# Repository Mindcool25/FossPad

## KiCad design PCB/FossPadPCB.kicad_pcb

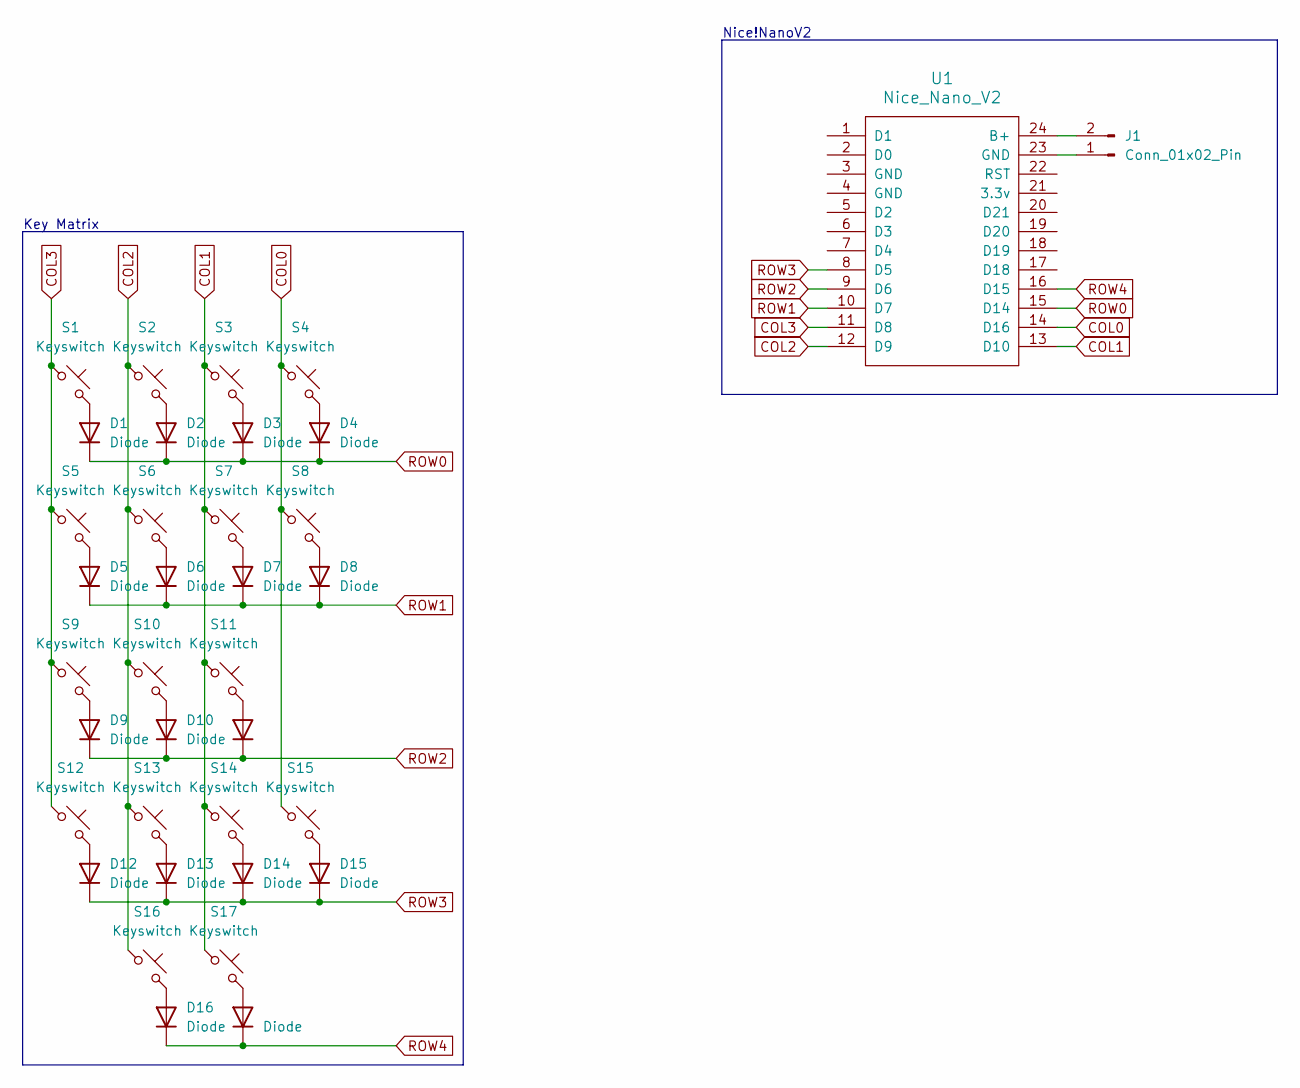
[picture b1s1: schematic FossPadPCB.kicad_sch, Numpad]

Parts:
D1, D2, D3, D4, D5, D6, D7, D8, D9, D10, D11, D12, D13, D14, D15, D16, D17: Diode; Diode_DO-35
J1: Conn_01x02_Pin; JWT_A3963_1x02_P3.96mm_Vertical
S1, S2, S3, S4, S5, S6, S7, S9, S10, S11, S12, S13, S14, S17: Keyswitch; MX_PCB_1.00u
S8, S15: Keyswitch; MX_PCB_2.00u_90deg
S16: Keyswitch; MX_PCB_2.00u
U1: Nice_Nano_V2

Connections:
COL0: S4.1, S8.1, S15.1, U1.14 (D16)
COL1: S3.1, S7.1, S11.1, S14.1, S17.1, U1.13 (D10)
COL2: S2.1, S6.1, S10.1, S13.1, S16.1, U1.12 (D9)
COL3: S1.1, S5.1, S9.1, S12.1, U1.11 (D8)
unnamed: D1.2 (A), S1.2
unnamed: D2.2 (A), S2.2
unnamed: D3.2 (A), S3.2
unnamed: D4.2 (A), S4.2
unnamed: D5.2 (A), S5.2
unnamed: D6.2 (A), S6.2
unnamed: D7.2 (A), S7.2
unnamed: D8.2 (A), S8.2
unnamed: D9.2 (A), S9.2
unnamed: D10.2 (A), S10.2
unnamed: D11.2 (A), S11.2
unnamed: D12.2 (A), S12.2
unnamed: D13.2 (A), S13.2
unnamed: D14.2 (A), S14.2
unnamed: D15.2 (A), S15.2
unnamed: D16.2 (A), S16.2
unnamed: D17.2 (A), S17.2
unnamed: J1.1, U1.23 (GND)
unnamed: J1.2, U1.24 (B+)
ROW0: D1.1 (K), D2.1 (K), D3.1 (K), D4.1 (K), U1.15 (D14)
ROW1: D5.1 (K), D6.1 (K), D7.1 (K), D8.1 (K), U1.10 (D7)
ROW2: D9.1 (K), D10.1 (K), D11.1 (K), U1.9 (D6)
ROW3: D12.1 (K), D13.1 (K), D14.1 (K), D15.1 (K), U1.8 (D5)
ROW4: D16.1 (K), D17.1 (K), U1.16 (D15)

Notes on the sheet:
Key Matrix
Nice!NanoV2

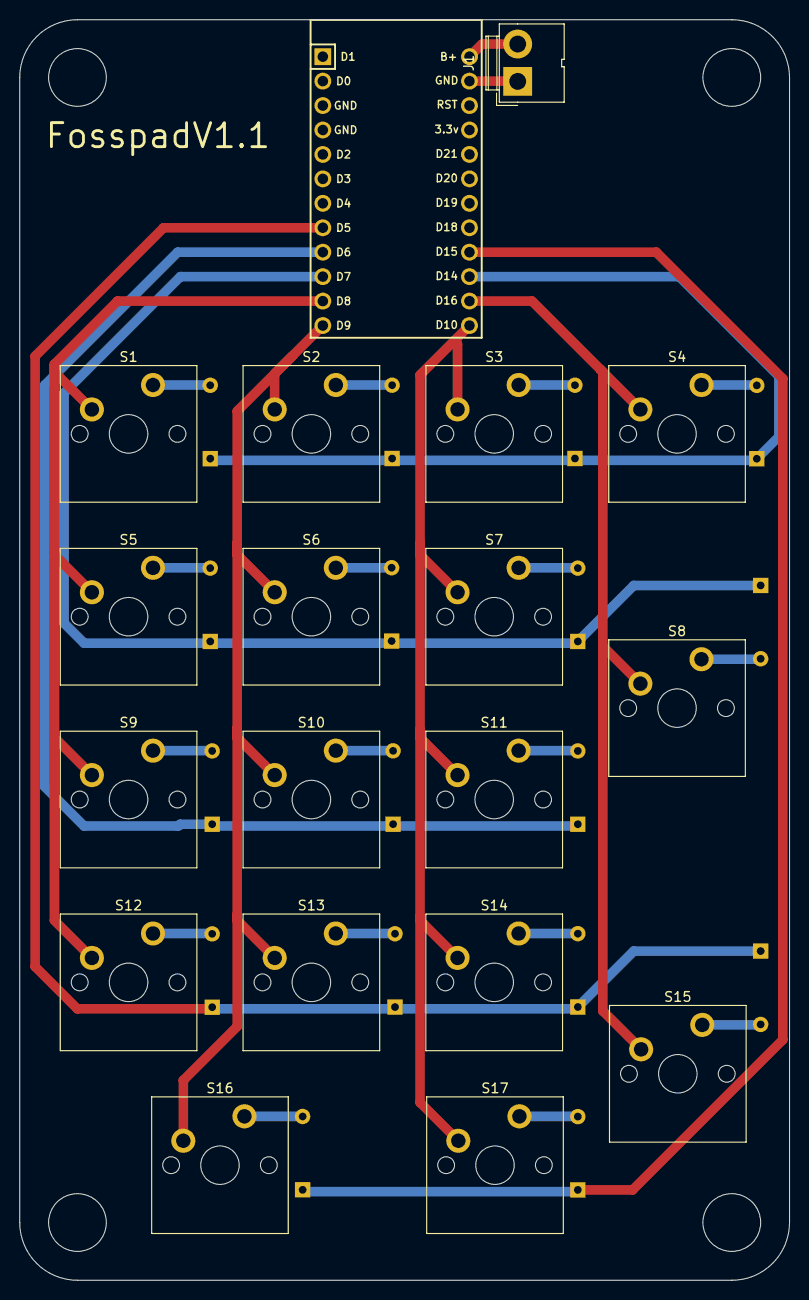
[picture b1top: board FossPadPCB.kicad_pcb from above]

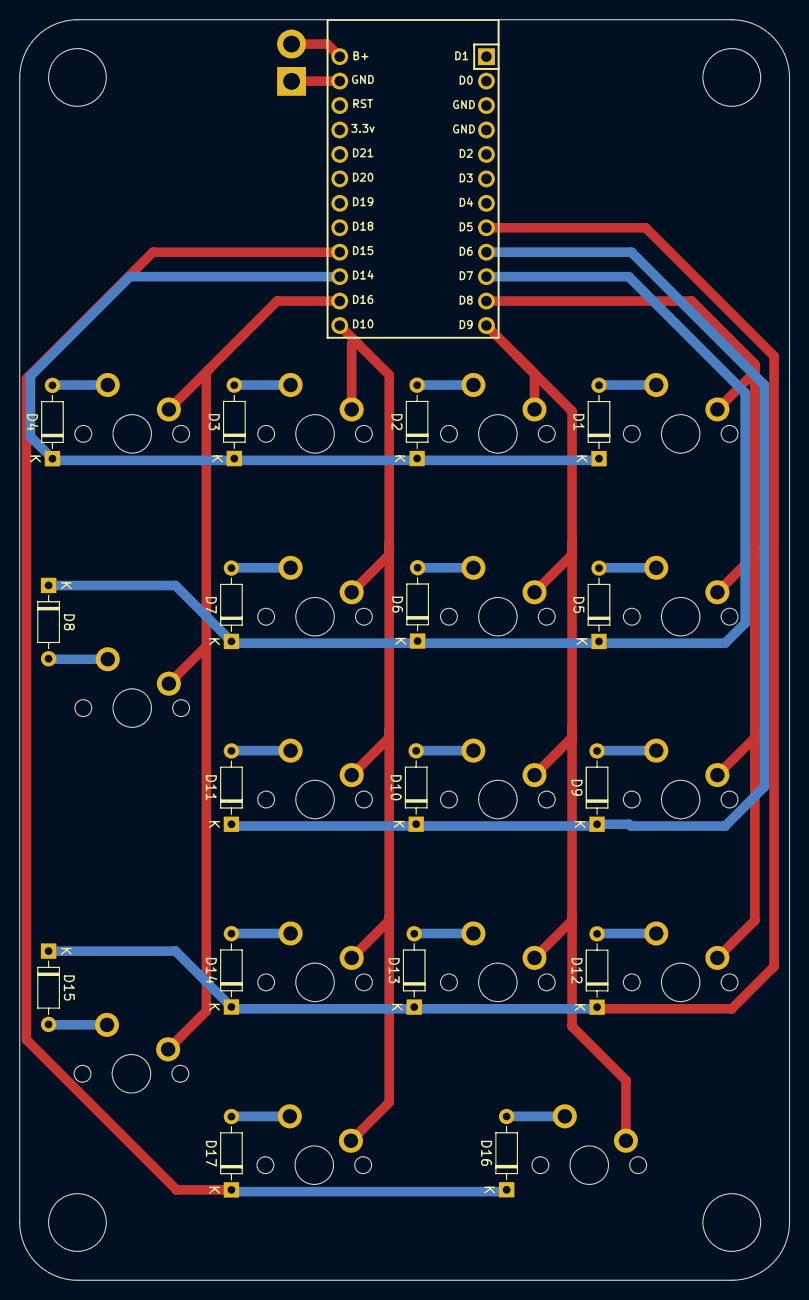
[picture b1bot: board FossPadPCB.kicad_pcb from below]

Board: 2 copper layers, 80.0 x 131.0 mm, 36 parts (17 on the bottom side), 28 nets.

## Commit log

2024-07-06 Moving github actions to top dir
2024-07-06 Fixing actions?
2024-07-06 More messing with github actions
2024-07-06 Fixing all the things
